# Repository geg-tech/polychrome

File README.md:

# polychrome
A custom printed ID badge holder with diffused rgb leds

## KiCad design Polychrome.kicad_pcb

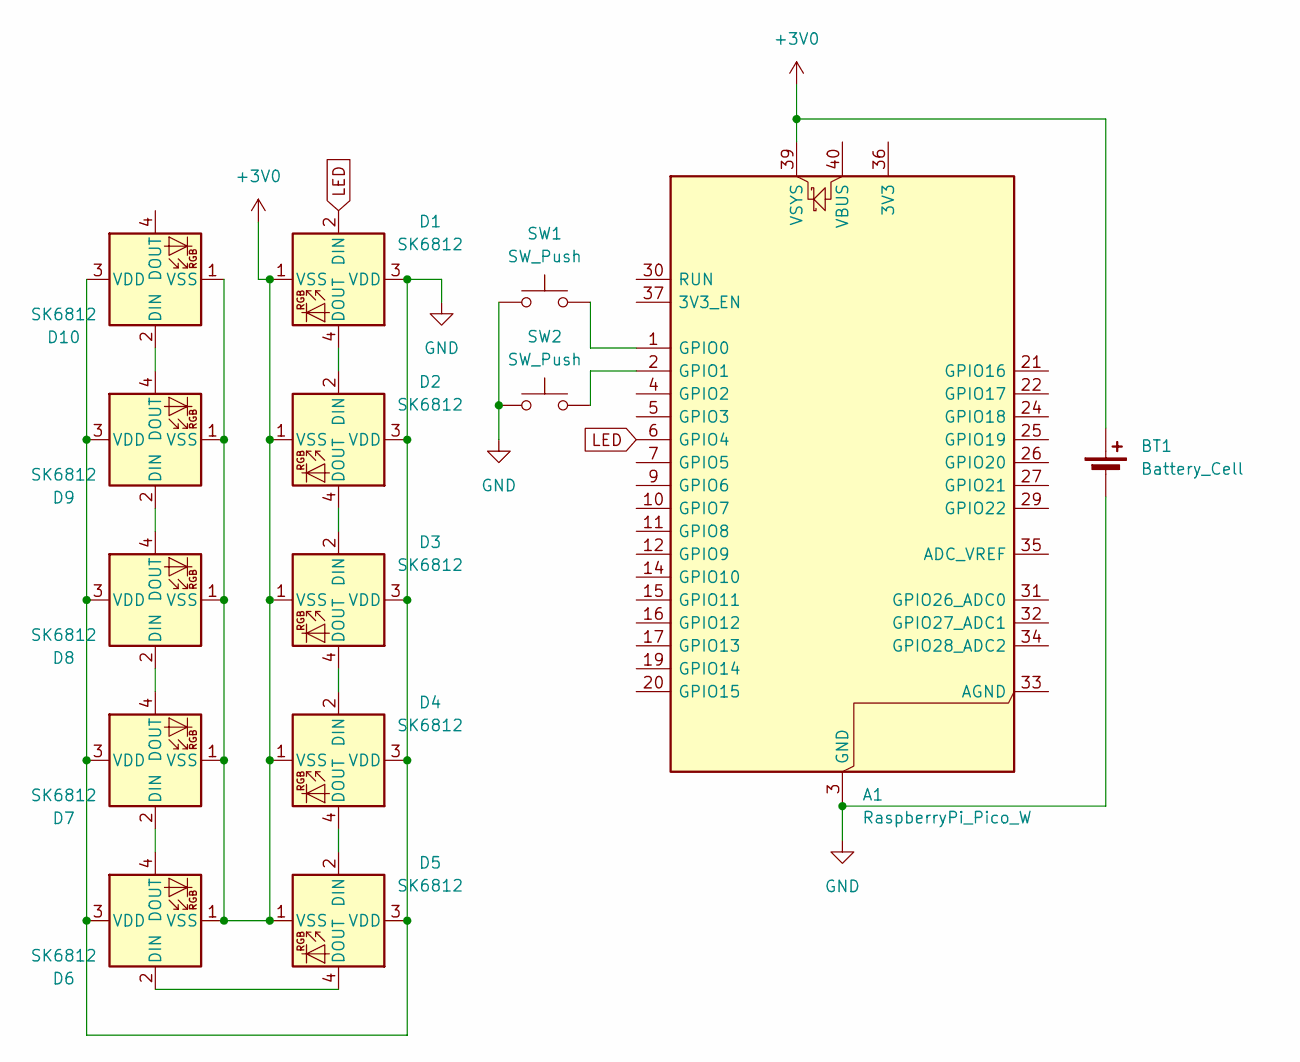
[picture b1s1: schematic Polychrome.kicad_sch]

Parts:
A1: RaspberryPi_Pico_W; RaspberryPi_Pico_W_SMD_HandSolder
BT1: Battery_Cell; BatteryHolder_Keystone_3034_1x20mm
D1, D2, D3, D4, D5, D6, D7, D8, D9, D10: SK6812; LED_SK6812_PLCC4_5.0x5.0mm_P3.2mm
SW1, SW2: SW_Push; SW_PUSH-12mm

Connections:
+3V0: A1.39 (VSYS), BT1.1 (+), D1.1 (VSS), D2.1 (VSS), D3.1 (VSS), D4.1 (VSS), D5.1 (VSS), D6.1 (VSS), D7.1 (VSS), D8.1 (VSS), D9.1 (VSS), D10.1 (VSS)
GND: A1.3 (GND), A1.8 (GND), A1.13 (GND), A1.18 (GND), A1.23 (GND), A1.28 (GND), A1.38 (GND), BT1.2 (-), D1.3 (VDD), D2.3 (VDD), D3.3 (VDD), D4.3 (VDD), D5.3 (VDD), D6.3 (VDD), D7.3 (VDD), D8.3 (VDD), D9.3 (VDD), D10.3 (VDD), SW1.1, SW2.1
LED: A1.6 (GPIO4), D1.2 (DIN)
unnamed: A1.1 (GPIO0), SW1.2
unnamed: A1.2 (GPIO1), SW2.2
unnamed: D1.4 (DOUT), D2.2 (DIN)
unnamed: D2.4 (DOUT), D3.2 (DIN)
unnamed: D3.4 (DOUT), D4.2 (DIN)
unnamed: D4.4 (DOUT), D5.2 (DIN)
unnamed: D5.4 (DOUT), D6.2 (DIN)
unnamed: D6.4 (DOUT), D7.2 (DIN)
unnamed: D7.4 (DOUT), D8.2 (DIN)
unnamed: D8.4 (DOUT), D9.2 (DIN)
unnamed: D9.4 (DOUT), D10.2 (DIN)

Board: 2 copper layers, 14 parts (0 on the bottom side), 14 nets, no tracks yet.
